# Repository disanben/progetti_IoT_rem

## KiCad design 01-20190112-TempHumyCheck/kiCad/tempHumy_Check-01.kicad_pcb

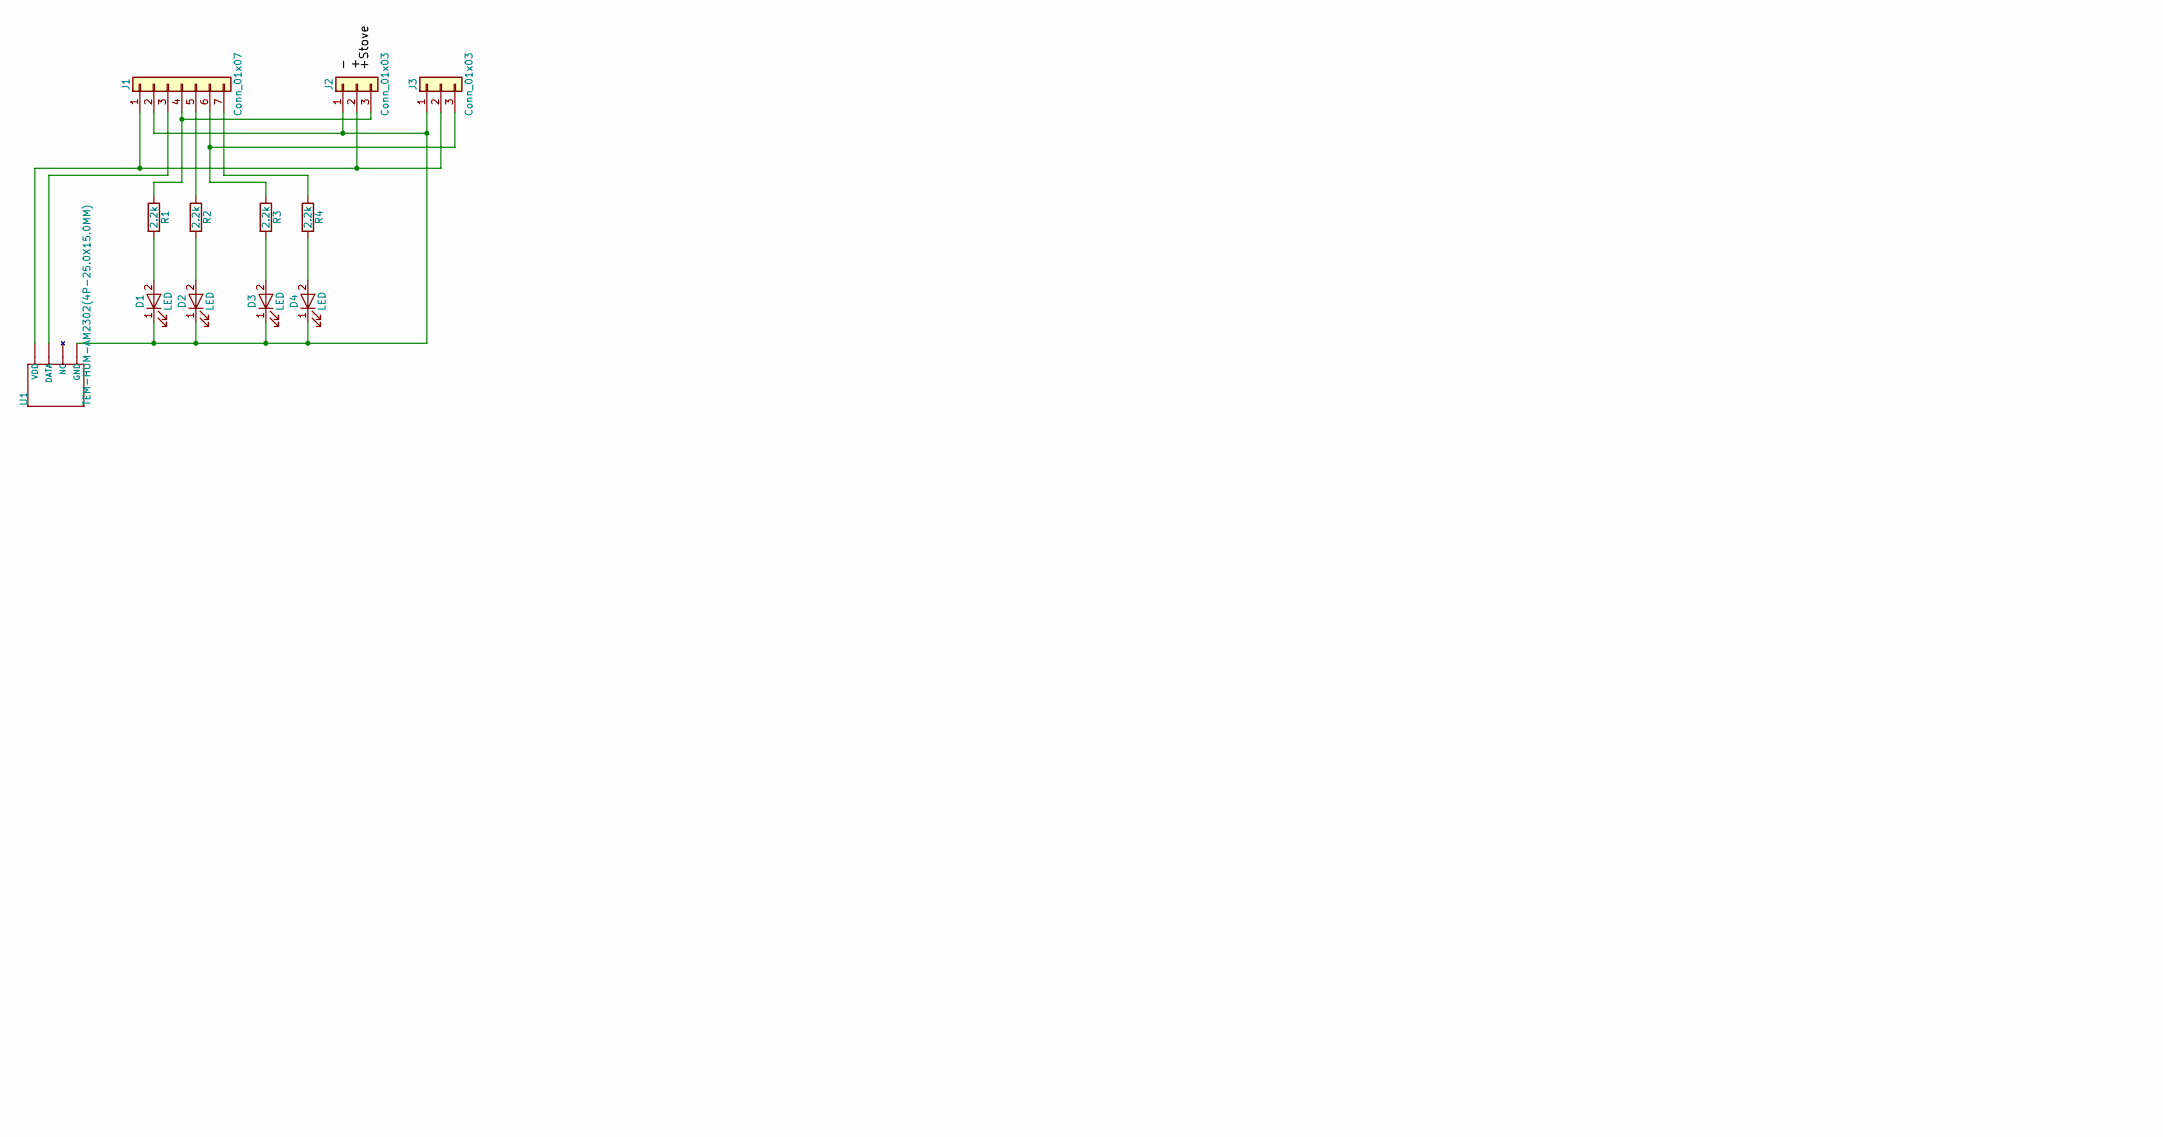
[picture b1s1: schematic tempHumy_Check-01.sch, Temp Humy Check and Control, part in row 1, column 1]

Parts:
D1, D2, D3, D4: LED; LED_D3.0mm
J1: Conn_01x07; Pin_Header_Straight_1x07_Pitch2.54mm
J2, J3: Conn_01x03; Pin_Header_Straight_1x03_Pitch2.54mm
R1, R2, R3, R4: 2.2k; R_Axial_DIN0414_L11.9mm_D4.5mm_P20.32mm_Horizontal
U1: TEM-HUM-AM2302(4P-25.0X15.0MM); SNR4-2.54-25.0X15.0X7.0MM

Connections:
unnamed: D1.1 (K), D2.1 (K), D3.1 (K), D4.1 (K), J1.2, J2.1, J3.1, U1.P$4 (GND)
unnamed: D1.2 (A), R1.2
unnamed: D2.2 (A), R2.2
unnamed: D3.2 (A), R3.2
unnamed: D4.2 (A), R4.2
unnamed: J1.1, J2.2, J3.2, U1.P$1 (VDD)
unnamed: J1.3, U1.P$2 (DATA)
unnamed: J1.4, J2.3, R1.1
unnamed: J1.5, R2.1
unnamed: J1.6, J3.3, R3.1
unnamed: J1.7, R4.1

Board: 2 copper layers, 12 parts (0 on the bottom side), 11 nets, no tracks yet.

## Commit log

2019-03-02 Primo Commit
2019-03-04 Aggiornamento per TempHumyCheck
2019-03-05 Avanzamento contenitore
2019-03-05 Altri passetti avanti sul contenitore
2019-03-06 Modifiche
2019-03-16 Inserito progetto in eclipse
2019-03-17 cancellato per errore
